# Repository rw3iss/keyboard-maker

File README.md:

# Keyboard Builder (keybuild)

A config-driven toolchain for designing and building custom mechanical keyboards from scratch. Takes a keyboard layout and component choices as input, generates KiCad schematics, PCB layouts, switch plates, 3D-printable cases, ZMK firmware, and a bill of materials — all from a single CLI tool. Includes a 3D web viewer for visualizing the assembled keyboard.

<p>

</p>

## Quick Start

```bash
# 1. Install prerequisites
./src/scripts/setup.sh

# 2. Install toolchain dependencies
cd src/tools && npm install

# 3. Run the interactive wizard
npx keybuild wizard
```

The wizard walks you through every design choice (layout, switches, MCU, connectivity, features, routing) and generates all project files into `projects/<name>/`.

## Features

### Interactive CLI Wizard

The main way to use the toolchain. Prompts you step-by-step through:

- **Layout** — point to a local KLE JSON file, paste a keyboard-layout-editor.com URL, or pick a built-in template
- **Switches** — browse supported switch families and variants, with detailed spec sheets for each
- **MCU** — select from supported nRF52840 modules with feature summaries and info screens
- **Connectivity** — USB-C (always on) + optional Bluetooth
- **Power** — battery capacity, charger IC selection with detailed comparisons
- **Features** — per-key RGB (above or below switch), underglow, rotary encoder
- **Physical layout** — USB port side (left/back/right), connector position and order, case height profile
- **PCB layers** — 2-layer (standard) or 4-layer (dedicated signal/power planes). For 4-layer, choose which inner layer carries the main switch traces
- **PCB routing** — auto (Freerouting), guided (generates instructions), or manual
- **Outputs** — checkbox selection of which files to generate

The confirmation screen shows estimated keyboard dimensions with an ASCII side-profile diagram before you proceed.

### Config-Driven Generation

Every build produces a `build-config.json` at the project root. You can re-run or tweak builds without the wizard:

```bash
cd src/tools

# Generate from an existing project config (no prompts)
npx keybuild generate --config ../../projects/blue-dream-space/build-config.json

# Re-generate and overwrite existing build
npx keybuild generate --config ../../projects/my-keyboard/build-config.json --overwrite

# Validate a config and see design warnings
npx keybuild validate --config ../../projects/my-keyboard/build-config.json
```

You can also pass a partial config to the wizard — it skips questions that are already answered:

```bash
npx keybuild wizard --config ./my-partial-config.json
npx keybuild wizard --kle-file ../../projects/my-keyboard/my-layout.json
```

### Project Output Structure

Each project gets its own folder under `projects/`:

```
projects/blue-dream-space/
├── blue-dream-space-kle.json       # KLE layout file
├── build-config.json               # Full build config (re-runnable)
├── config/                         # Additional config files
└── build/                          # Generated artifacts
    ├── *.kicad_sch                 # KiCad schematic (with embedded symbols)
    ├── *.kicad_pcb                 # KiCad PCB layout
    ├── *-plate.dxf                 # Laser-cut switch plate (DXF)
    ├── *-plate.scad / *-plate.stl  # 3D-printable plate (OpenSCAD + STL)
    ├── *-case.scad / *-case.stl    # 3D-printable case (OpenSCAD + STL)
    ├── *.step                      # PCB STEP file (for 3D assembly)
    ├── *-preview.svg               # 2D PCB preview (copper + silkscreen)
    ├── *-3d.png                    # 3D ray-traced PCB render
    ├── routing-guide.md            # PCB routing instructions
    ├── firmware/                   # ZMK firmware configs
    │   ├── *.overlay               # Devicetree overlay
    │   ├── *.keymap                # Default keymap
    │   ├── *.conf                  # Feature flags
    │   └── *.zmk.yml              # Shield metadata
    ├── bom.md / bom.csv            # Bill of materials
    ├── gerbers/                    # Gerber + drill files (if KiCad CLI available)
    ├── overview.html               # Project overview page (open in browser)
    ├── viewer.html                 # Standalone 3D viewer (no server needed)
    ├── design-notes.txt            # Warnings and design concerns
    └── build.log                   # Build parameters
```

### Preview & Validation

```bash
cd src/tools

# Generate 2D SVG + 3D PNG preview of a PCB
npx keybuild preview --pcb ../../projects/my-keyboard/build/my-keyboard.kicad_pcb

# Run Design Rule Check
npx keybuild drc --pcb ../../projects/my-keyboard/build/my-keyboard.kicad_pcb

# Export PCB as STEP for 3D assembly
npx keybuild export-step --pcb ../../projects/my-keyboard/build/my-keyboard.kicad_pcb
```

The `preview` command produces a layered SVG (copper, silkscreen, edge cuts) and a ray-traced 3D PNG using KiCad's built-in renderer.

The `drc` command reports violations, unconnected pads, errors, and warnings — useful for validating PCBs before fabrication.

### Project Overview Page

Each build generates an `overview.html` — open it directly in a browser for a complete project dashboard:

- **Specs table** — all key parameters (switches, MCU, battery, GPIO usage, matrix, etc.)
- **Physical dimensions** — width, depth, front/rear height with ASCII side profile
- **Design notes** — color-coded warnings and info from the validator
- **Embedded 3D viewer** — interactive Three.js viewer with layer toggles, inline in the page
- **File browser** — all generated artifacts with inline image previews, code previews for text files, and download links

A standalone `viewer.html` is also generated — works without a server by embedding the config directly.

### 3D Web Viewer

Visualize your keyboard build in 3D directly in the browser:

```bash
# Option 1: Open the standalone viewer directly
xdg-open projects/blue-dream-space/build/viewer.html

# Option 2: Start the server-based viewer (supports live file loading)
cd src/tools
npx keybuild viewer --dir ../../projects/blue-dream-space/build
```

The viewer provides:
- **Layer toggles** — show/hide PCB, plate, case, switches, keycaps independently
- **Info panel** — project name, key count, matrix size, switch type, MCU
- **Orbit controls** — drag to rotate, scroll to zoom, right-drag to pan
- Reads the actual KLE layout for accurate key positioning and sizes

### 3D Case & Plate Generation

The build pipeline automatically generates parametric OpenSCAD files for the switch plate and case:

- **Plate** — rounded corners, per-key switch cutouts, stabilizer cutouts for wide keys, smart-positioned mounting holes
- **Case** — matching outline with walls, USB-C cutout on configurable side, battery compartment (if BLE), minimal front height with no standoffs for the thinnest possible profile

Mounting holes are positioned using a smart algorithm that finds empty areas between switches — no screws will overlap with any component.

If OpenSCAD is installed, STL files are compiled automatically. Otherwise, `.scad` files are output for manual compilation.

The `.scad` files are parametric — edit them to adjust wall thickness, corner radius, heights, etc.

### 3D Assembly (FreeCAD)

For a combined 3D model of the full keyboard assembly:

```bash
freecadcmd src/tools/src/3d-assembler/assemble.py \
  --pcb projects/my-keyboard/build/my-keyboard.step \
  --plate projects/my-keyboard/build/my-keyboard-plate.stl \
  --case projects/my-keyboard/build/my-keyboard-case.stl \
  --output projects/my-keyboard/build/assembled.step
```

Positions the PCB, plate, and case at correct heights and exports a combined STEP.

### PCB Routing

Three modes, selectable in the config or wizard:

- **`auto`** — Exports to Specctra DSN (via KiCad Python API), runs [Freerouting](https://github.com/freerouting/freerouting) headless, imports routed traces back. Falls back gracefully if tools aren't installed.
- **`guided`** — Generates a detailed routing guide with trace priority order, layer assignments, and width recommendations. Includes instructions for running Freerouting manually.
- **`manual`** — Outputs the unrouted PCB + routing guide. You handle routing entirely in KiCad.

* Note: The automated freerouting will not complete, usually. In normal circuits, it will get hung up on the last 5 traces or so. This is expected.
Instead of "auto" freerouting from the wizard, you should run the Freerouting manually after a build (as the Build Output will explain, if it can't complete).
For example, with the latest freerouting jar:
1. Run: java -jar /home/<user>/.local/bin/freerouting-2.1.0.jar -de <keybuild-root>/projects/<project>/build/keyboard.dsn
(then click 'Start the auto-router', in the opened freerouter window, and wait... it will take 5-15 minutes or so)
2. In Freerouting GUI: File → Export Specctra Session
3. Save as: <keybuild-root>/projects/<project>/build/keyboard.ses
4. Then import in KiCad PCB: File → Import → Specctra Session

### Component Database

All supported components live in `data/` as JSON files. The wizard loads these to populate its selection menus with detailed spec sheets, and the BOM generator pulls prices and supplier links from them.

```bash
cd src/tools

# Browse available components
npx keybuild list-components
npx keybuild list-components --type switches
npx keybuild list-components --type mcus
```

**Supported switches:** Kailh Choc v1/v2, Cherry MX ULP, Cherry MX, Gateron Low Profile
**Supported MCUs:** nice!nano v2, Seeed XIAO BLE, SuperMini nRF52840, Holyiot 18010, bare nRF52840

Adding a new component: create a JSON file in the appropriate `data/` subdirectory following the existing format. It will automatically appear in the wizard with its specs and supplier info.

### ZMK Firmware

Generated firmware configs are ready to build with ZMK:

```bash
# Build firmware (requires west/Zephyr — installed by setup.sh)
cd src/firmware
./build.sh blue_dream_space nice_nano_v2

# Flash to keyboard
./flash.sh ../../projects/firmware-builds/blue_dream_space_nice_nano_v2.uf2
```

The flash script auto-detects the bootloader drive. Double-tap reset on your board to enter bootloader mode.

### KLE Layout Renderer

The build pipeline automatically generates an SVG rendering of your keyboard layout from the KLE JSON file. The image is saved to `build/images/kle-layout.svg` and shown in the web wizard's Overview and Layout config pages.

If `sharp` is installed (`npm install sharp` in src/tools), the renderer also produces a PNG version. Otherwise SVG is used — both work in browsers and the overview HTML.

### Web Wizard (GUI)

A full web application alternative to the CLI wizard:

```bash
cd src/wizard
npm install
npm run dev
```

Opens at `http://localhost:5173` with:
- **File menu** — New/Open/Save projects, About
- **Overview tab** — all config steps with completion status, layout preview image
- **Config tab** — select options for each step with product detail pages for every component
- **Build tab** — trigger generation with SSE progress streaming, view output files
- **Layout Editor** — 2D canvas for repositioning screws, USB, MCU with drag-and-drop
- **Part Detail Pages** — `/parts/:category/:id` with full specs, features, concerns, supplier links

The web wizard shares the same backend generators as the CLI and saves to the same project files.

## CLI Command Reference

All commands run from `src/tools/`:

| Command | Description |
|---------|-------------|
| `npx keybuild wizard` | Interactive build wizard |
| `npx keybuild generate -c <config>` | Generate from config file (no prompts) |
| `npx keybuild validate -c <config>` | Validate config and show design concerns |
| `npx keybuild list-components` | Browse component database |
| `npx keybuild preview -p <pcb>` | Render 2D SVG + 3D PNG of PCB |
| `npx keybuild drc -p <pcb>` | Run Design Rule Check |
| `npx keybuild export-step -p <pcb>` | Export PCB as STEP file |
| `npx keybuild viewer -d <build-dir>` | Start 3D web viewer |

## Directory Structure

```
├── projects/         User projects — each with layout, config, and build output
├── data/             Component database (JSON files for switches, MCUs, etc.)
├── src/
│   ├── tools/        Node.js/TypeScript toolchain (Keybuild CLI)
│   │   └── src/
│   │       ├── cli/              Interactive wizard and commands
│   │       ├── kle-parser/       KLE JSON layout parser
│   │       ├── matrix-generator/ Switch matrix optimizer
│   │       ├── kicad-generator/  Schematic + PCB generators
│   │       ├── plate-generator/  DXF plate generator
│   │       ├── case-generator/   OpenSCAD case/plate 3D generator
│   │       ├── firmware-generator/ ZMK config generator
│   │       ├── bom-generator/    Bill of materials generator
│   │       ├── routing/          PCB auto-routing (Freerouting integration)
│   │       ├── preview/          SVG/PNG preview and DRC
│   │       ├── viewer/           Three.js 3D web viewer
│   │       ├── 3d-assembler/     FreeCAD assembly script
│   │       ├── overview-generator/ Project overview HTML generator
│   │       └── build/            Build orchestrator
│   ├── firmware/     ZMK firmware workspace + build/flash scripts
│   └── scripts/      Setup and prerequisite installation scripts
└── docs/             Design research and reference documents
```

## Prerequisites

Run `./src/scripts/setup.sh` to install everything, or install manually:

| Tool | Required | Purpose |
|------|----------|---------|
| **Node.js 20+** | Yes | Runs the toolchain |
| **KiCad 9+** | Optional | Gerber/STEP export, 3D render, DRC, PCB editing |
| **OpenSCAD** | Optional | Compiles parametric case/plate to STL |
| **Java 11+** | Optional | Runs Freerouting (auto-routing) |
| **Freerouting** | Optional | Automated PCB trace routing |
| **FreeCAD** | Optional | 3D model assembly (PCB + case + plate) |
| **west (Zephyr)** | Optional | Building ZMK firmware from source |

Check what's installed:

```bash
./src/scripts/setup-check.sh
```

The toolchain generates KiCad and OpenSCAD files without those tools installed — you only need them to open/edit the files, compile STLs, or export Gerbers.

## Design Decisions

- **nRF52840** — Single chip with native USB 2.0 + BLE 5.0. No external radio module needed.
- **ZMK firmware** — First-class wireless support, built on Zephyr RTOS. Auto-switches between USB and BLE.
- **Dual switch support** — Same electrical matrix, different physical footprints. Select via config.
- **Config-driven** — Everything flows from one JSON. Change it, re-run, get new files.
- **Smart matrix optimizer** — Automatically rebalances the switch matrix to fit within the selected MCU's GPIO count. An 86-key layout fits on a 21-GPIO nice!nano (11x10 matrix).
- **Multi-layer PCB** — Supports 2-layer (standard, most affordable) and 4-layer boards (dedicated signal/power planes, better routing). For 4-layer, you choose which inner layer carries the main switch traces — the autorouter and routing guide adapt accordingly.
- **KiCad 9 native** — Generated schematics embed symbol definitions from your installed KiCad libraries. PCB files use the v20240108 format with proper quoting and layer definitions.
- **Thin profile** — Default case height is minimal: 0.8mm case bottom + 1.6mm PCB + 1.5mm plate = ~3.9mm front. No standoffs at the front edge. Rear is slightly taller for USB clearance. User can customize both heights.
- **Smart screw placement** — Mounting holes are automatically positioned to avoid all switches and components, staying as close to corners and midpoints as possible while maintaining clearance.

## Tips

- The **nice!nano v2** has 21 GPIOs. The matrix optimizer handles layouts up to ~100 keys on 21 GPIOs by rebalancing rows/columns automatically.
- Cherry MX **ULP switches** require reflow soldering and SLA-printed keycaps. The wizard flags this automatically.
- The `build-config.json` at each project root is re-runnable. Edit it and pass it back to `generate` for quick iterations.
- Run `validate` on a config before `generate` to catch issues early — it checks GPIO budgets, charging rates, switch/hot-swap compatibility, etc.
- Layouts from [keyboard-layout-editor.com](http://www.keyboard-layout-editor.com/) — use the "Download JSON" button and save into your project folder.
- If a build already exists, the tool will warn you. Use `--overwrite` to replace it silently.
- The 3D viewer reads your actual KLE layout for accurate key positioning — works best when `layout.json` is in the build directory.
- **4-layer boards** significantly improve auto-routing success. A 2-layer board may leave 5-10 unrouted connections (typically MCU power pins) that need manual cleanup. A 4-layer board with signal traces on In1.Cu often routes 100%.
- Per-key RGB LEDs can be placed **above** (for shine-through keycaps) or **below** (reverse-mount, light shines through PCB) the switch — the wizard asks during setup.
- USB port can be placed on the **left**, **right**, or **back** edge. For back placement, choose left/center/right position and USB-first or power-first order.
- Open `overview.html` from any build for a complete project dashboard — no server needed, works directly in the browser.

## Running Tests

```bash
cd src/tools && npm test
```

## Contributing

Contributions are welcome! Feel free to try out the toolchain, explore the codebase, and submit improvements.

**How to contribute:**

1. Fork the repo and create a feature branch (`git checkout -b my-feature`)
2. Make your changes, ensuring tests pass (`cd src/tools && npm test`)
3. Submit a Pull Request describing what you changed and why

Bug fixes, feature implementations, documentation improvements, and new component data are all appreciated. Please keep PRs focused — one feature or fix per PR.

**Using AI assistants is recommended.** This project was largely built with [Claude Code](https://claude.ai/code) (Claude Opus 4.6) and is well-suited for AI-assisted development. The repo includes a `CLAUDE.md` file at the root with up-to-date project context, architecture decisions, and build instructions — it's automatically loaded by Claude Code and provides good initial context for any AI assistant working on the codebase.

If you're using Claude Code or another AI tool, point it at `CLAUDE.md` first to get oriented, then explore the implementation plan at `.claude/plans/` for deeper architectural context.

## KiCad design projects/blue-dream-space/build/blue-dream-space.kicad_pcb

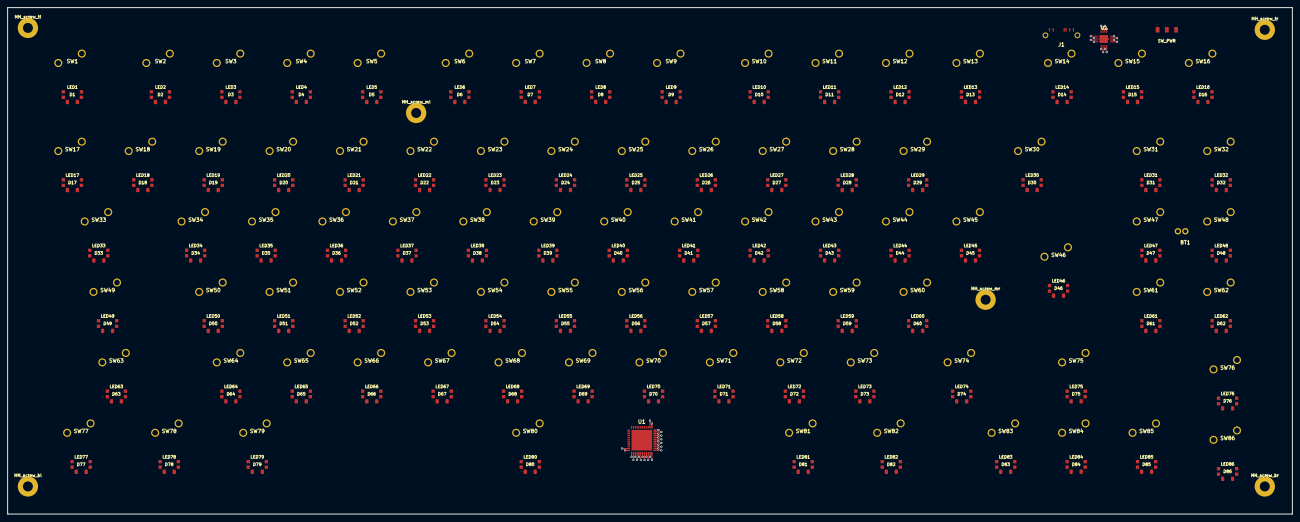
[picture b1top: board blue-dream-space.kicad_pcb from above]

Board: 4 copper layers, 347.5 x 137.0 mm, 269 parts (0 on the bottom side), 28 nets.

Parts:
BT1: Battery; JST_PH_S2B-PH-K_1x02_P2.00mm_Horizontal
D1, D2, D3, D4, D5, D6, D7, D8, D9, D10, D11, D12, D13, D14, D15, D16, D17, D18, D19, D20, D21, D22, D23, D24, D25, D26, D27, D28, D29, D30, D31, D32, D33, D34, D35, D36, D37, D38, D39, D40, D41, D42, D43, D44, D45, D46, D47, D48, D49, D50, D51, D52, D53, D54, D55, D56, D57, D58, D59, D60, D61, D62, D63, D64, D65, D66, D67, D68, D69, D70, D71, D72, D73, D74, D75, D76, D77, D78, D79, D80, D81, D82, D83, D84, D85, D86: 1N4148; D_SOD-123
J1: USB_C; USB_C_Receptacle_GCT_USB4085
LED1, LED2, LED3, LED4, LED5, LED6, LED7, LED8, LED9, LED10, LED11, LED12, LED13, LED14, LED15, LED16, LED17, LED18, LED19, LED20, LED21, LED22, LED23, LED24, LED25, LED26, LED27, LED28, LED29, LED30, LED31, LED32, LED33, LED34, LED35, LED36, LED37, LED38, LED39, LED40, LED41, LED42, LED43, LED44, LED45, LED46, LED47, LED48, LED49, LED50, LED51, LED52, LED53, LED54, LED55, LED56, LED57, LED58, LED59, LED60, LED61, LED62, LED63, LED64, LED65, LED66, LED67, LED68, LED69, LED70, LED71, LED72, LED73, LED74, LED75, LED76, LED77, LED78, LED79, LED80, LED81, LED82, LED83, LED84, LED85, LED86: SK6812MINI-E; LED_SK6812MINI-E
MH_screw_bl: MountingHole_M2.5; MountingHole_2.7mm_M2.5_Pad_Via
MH_screw_br: MountingHole_M2.5; MountingHole_2.7mm_M2.5_Pad_Via
MH_screw_ml: MountingHole_M2.5; MountingHole_2.7mm_M2.5_Pad_Via
MH_screw_mr: MountingHole_M2.5; MountingHole_2.7mm_M2.5_Pad_Via
MH_screw_tl: MountingHole_M2.5; MountingHole_2.7mm_M2.5_Pad_Via
MH_screw_tr: MountingHole_M2.5; MountingHole_2.7mm_M2.5_Pad_Via
SW1, SW2, SW3, SW4, SW5, SW6, SW7, SW8, SW9, SW10, SW11, SW12, SW13, SW14, SW15, SW16, SW17, SW18, SW19, SW20, SW21, SW22, SW23, SW24, SW25, SW26, SW27, SW28, SW29, SW30, SW31, SW32, SW33, SW34, SW35, SW36, SW37, SW38, SW39, SW40, SW41, SW42, SW43, SW44, SW45, SW46, SW47, SW48, SW49, SW50, SW51, SW52, SW53, SW54, SW55, SW56, SW57, SW58, SW59, SW60, SW61, SW62, SW63, SW64, SW65, SW66, SW67, SW68, SW69, SW70, SW71, SW72, SW73, SW74, SW75, SW76, SW77, SW78, SW79, SW80, SW81, SW82, SW83, SW84, SW85, SW86: SW_Push
SW_PWR: Power; SW_SPDT_CK-JS102011SAQN
U1: STM32WB55; QFN-48-1EP_7x7mm_P0.5mm_EP5.6x5.6mm
U2: bq24075; QFN-16-1EP_3.5x3.5mm_P0.5mm_EP2.15x2.15mm

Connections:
COL0: D1.2, D17.2, D33.2, D49.2, D63.2, D77.2, SW1.1, SW17.1, SW33.1, SW49.1, SW63.1, SW77.1, U1.7
COL1: D2.2, D18.2, D34.2, D50.2, D64.2, D78.2, SW2.1, SW18.1, SW34.1, SW50.1, SW64.1, SW78.1, U1.8
COL2: D3.2, D19.2, D35.2, D51.2, D65.2, D79.2, SW3.1, SW19.1, SW35.1, SW51.1, SW65.1, SW79.1, U1.9
COL3: D4.2, D20.2, D36.2, D52.2, D66.2, D80.2, SW4.1, SW20.1, SW36.1, SW52.1, SW66.1, SW80.1, U1.12
COL4: D5.2, D21.2, D37.2, D53.2, D67.2, D81.2, SW5.1, SW21.1, SW37.1, SW53.1, SW67.1, SW81.1, U1.13
COL5: D6.2, D22.2, D38.2, D54.2, D68.2, D82.2, SW6.1, SW22.1, SW38.1, SW54.1, SW68.1, SW82.1, U1.16
COL6: D7.2, D23.2, D39.2, D55.2, D69.2, D83.2, SW7.1, SW23.1, SW39.1, SW55.1, SW69.1, SW83.1, U1.17
COL7: D8.2, D24.2, D40.2, D56.2, D70.2, D84.2, SW8.1, SW24.1, SW40.1, SW56.1, SW70.1, SW84.1, U1.18
COL8: D9.2, D25.2, D41.2, D57.2, D71.2, D85.2, SW9.1, SW25.1, SW41.1, SW57.1, SW71.1, SW85.1, U1.19
COL9: D10.2, D26.2, D42.2, D58.2, D72.2, D86.2, SW10.1, SW26.1, SW42.1, SW58.1, SW72.1, SW86.1, U1.20
COL10: D11.2, D27.2, D43.2, D59.2, D73.2, SW11.1, SW27.1, SW43.1, SW59.1, SW73.1, U1.21
COL11: D12.2, D28.2, D44.2, D60.2, D74.2, SW12.1, SW28.1, SW44.1, SW60.1, SW74.1, U1.22
COL12: D13.2, D29.2, D45.2, D61.2, D75.2, SW13.1, SW29.1, SW45.1, SW61.1, SW75.1, U1.23
COL13: D14.2, D30.2, D46.2, D62.2, D76.2, SW14.1, SW30.1, SW46.1, SW62.1, SW76.1, U1.24
COL14: D15.2, D31.2, D47.2, SW15.1, SW31.1, SW47.1, U1.25
COL15: D16.2, D32.2, D48.2, SW16.1, SW32.1, SW48.1, U1.26
GND: BT1.2, J1.A1, J1.B1, J1.S1, J1.S2, LED1.3, LED2.3, LED3.3, LED4.3, LED5.3, LED6.3, LED7.3, LED8.3, LED9.3, LED10.3, LED11.3, LED12.3, LED13.3, LED14.3, LED15.3, LED16.3, LED17.3, LED18.3, LED19.3, LED20.3, LED21.3, LED22.3, LED23.3, LED24.3, LED25.3, LED26.3, LED27.3, LED28.3, LED29.3, LED30.3, LED31.3, LED32.3, LED33.3, LED34.3, LED35.3, LED36.3, LED37.3, LED38.3, LED39.3, LED40.3, LED41.3, LED42.3, LED43.3, LED44.3, LED45.3, LED46.3, LED47.3, LED48.3, LED49.3, LED50.3, LED51.3, LED52.3, LED53.3, LED54.3, LED55.3, LED56.3, LED57.3, LED58.3, LED59.3, LED60.3, LED61.3, LED62.3, LED63.3, LED64.3, LED65.3, LED66.3, LED67.3, LED68.3, LED69.3, LED70.3, LED71.3, LED72.3, LED73.3, LED74.3, LED75.3, LED76.3, LED77.3, LED78.3, LED79.3, LED80.3, LED81.3, LED82.3, LED83.3, LED84.3, LED85.3, LED86.3, U1.14, U1.37, U1.49, U2.2, U2.EP
ROW0: D1.1, D2.1, D3.1, D4.1, D5.1, D6.1, D7.1, D8.1, D9.1, D10.1, D11.1, D12.1, D13.1, D14.1, D15.1, D16.1, SW1.2, SW2.2, SW3.2, SW4.2, SW5.2, SW6.2, SW7.2, SW8.2, SW9.2, SW10.2, SW11.2, SW12.2, SW13.2, SW14.2, SW15.2, SW16.2, U1.1
ROW1: D17.1, D18.1, D19.1, D20.1, D21.1, D22.1, D23.1, D24.1, D25.1, D26.1, D27.1, D28.1, D29.1, D30.1, D31.1, D32.1, SW17.2, SW18.2, SW19.2, SW20.2, SW21.2, SW22.2, SW23.2, SW24.2, SW25.2, SW26.2, SW27.2, SW28.2, SW29.2, SW30.2, SW31.2, SW32.2, U1.2
ROW2: D33.1, D34.1, D35.1, D36.1, D37.1, D38.1, D39.1, D40.1, D41.1, D42.1, D43.1, D44.1, D45.1, D46.1, D47.1, D48.1, SW33.2, SW34.2, SW35.2, SW36.2, SW37.2, SW38.2, SW39.2, SW40.2, SW41.2, SW42.2, SW43.2, SW44.2, SW45.2, SW46.2, SW47.2, SW48.2, U1.3
ROW3: D49.1, D50.1, D51.1, D52.1, D53.1, D54.1, D55.1, D56.1, D57.1, D58.1, D59.1, D60.1, D61.1, D62.1, SW49.2, SW50.2, SW51.2, SW52.2, SW53.2, SW54.2, SW55.2, SW56.2, SW57.2, SW58.2, SW59.2, SW60.2, SW61.2, SW62.2, U1.4
ROW4: D63.1, D64.1, D65.1, D66.1, D67.1, D68.1, D69.1, D70.1, D71.1, D72.1, D73.1, D74.1, D75.1, D76.1, SW63.2, SW64.2, SW65.2, SW66.2, SW67.2, SW68.2, SW69.2, SW70.2, SW71.2, SW72.2, SW73.2, SW74.2, SW75.2, SW76.2, U1.5
ROW5: D77.1, D78.1, D79.1, D80.1, D81.1, D82.1, D83.1, D84.1, D85.1, D86.1, SW77.2, SW78.2, SW79.2, SW80.2, SW81.2, SW82.2, SW83.2, SW84.2, SW85.2, SW86.2, U1.6
USB_DM: J1.A7, U1.11
USB_DP: J1.A6, U1.10
VBAT: BT1.1, SW_PWR.1, U2.3
VBUS: J1.A4, J1.B4, U2.1
VCC: LED1.1, LED2.1, LED3.1, LED4.1, LED5.1, LED6.1, LED7.1, LED8.1, LED9.1, LED10.1, LED11.1, LED12.1, LED13.1, LED14.1, LED15.1, LED16.1, LED17.1, LED18.1, LED19.1, LED20.1, LED21.1, LED22.1, LED23.1, LED24.1, LED25.1, LED26.1, LED27.1, LED28.1, LED29.1, LED30.1, LED31.1, LED32.1, LED33.1, LED34.1, LED35.1, LED36.1, LED37.1, LED38.1, LED39.1, LED40.1, LED41.1, LED42.1, LED43.1, LED44.1, LED45.1, LED46.1, LED47.1, LED48.1, LED49.1, LED50.1, LED51.1, LED52.1, LED53.1, LED54.1, LED55.1, LED56.1, LED57.1, LED58.1, LED59.1, LED60.1, LED61.1, LED62.1, LED63.1, LED64.1, LED65.1, LED66.1, LED67.1, LED68.1, LED69.1, LED70.1, LED71.1, LED72.1, LED73.1, LED74.1, LED75.1, LED76.1, LED77.1, LED78.1, LED79.1, LED80.1, LED81.1, LED82.1, LED83.1, LED84.1, LED85.1, LED86.1, SW_PWR.2, U1.15, U1.38, U2.4

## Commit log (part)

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2026-03-25 Initial commit, all stages basically working, with web editor.
2026-04-13 Update readme, screenshots, add switches, layout config tweaks.
2026-04-14 Add 3d viewer screenshot
2026-04-14 Screenshot update
